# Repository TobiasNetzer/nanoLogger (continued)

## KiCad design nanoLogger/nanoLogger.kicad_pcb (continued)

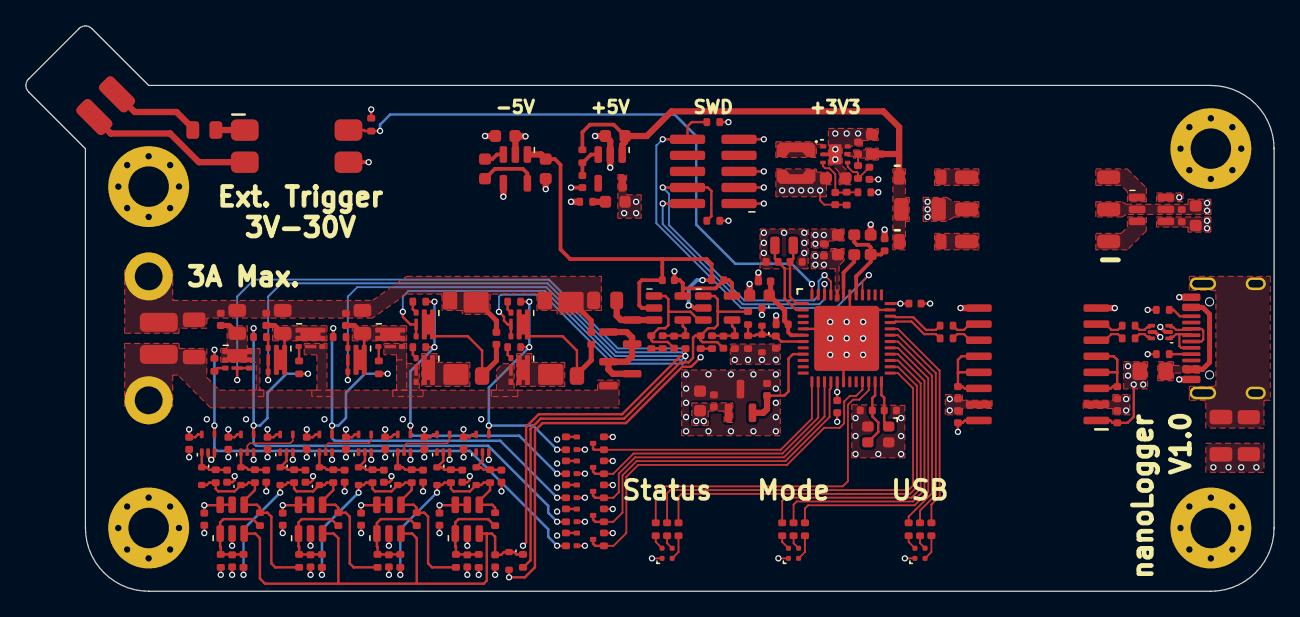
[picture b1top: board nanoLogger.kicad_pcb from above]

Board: 4 copper layers, 98.7 x 44.7 mm, 221 parts (0 on the bottom side), 128 nets.

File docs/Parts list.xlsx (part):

Position | Menge | Bauteilbezeichnung | Wert/Typ | Beschreibung | Hersteller | Hersteller-Nr. | Lieferant | Lieferant-Nr. | Stückpreis | Gesamtpreis
1 | 2 | C1, C35 | 10nF | 10nF-1%-1206-C0G-630V | Kemet | C1206C103FBGACAUTO | Mouser | 80-C1206C103FBGAUTO | 1.03 | 2.06
2 | 6 | C2, C8, C12, C19, C23, C27 | 10µF | 10µF-20%-0603-X5R-10V | Kemet | C0603C106M8PACTU | Mouser | 80-C0603C106M8PACTU | 0.43 | 2.58
3 | 33 | C3, C4, C5, C6, C7, C9, C10, C14, C20, C21, C22, C24, C26, C28, C36, C37, C38, 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 | 100nF | 100nF-20%-0402-X7R-25V | Kemet | C0402C104M3RACTU | Mouser | 80-C0402C104M3R | 0.26 | 8.58
4 | 7 | C11, C43, C44, C50, C51, C52, C53 | 22pF | 22pF-5%-0402-C0G-50V | Kemet | C0402C220J5GACTU | Mouser | 80-C0402C220J5G | 0.09 | 0.63
5 | 2 | C13, C15 | 2.2µF | 2.2µF-10%-0603-X5R-10V | Kemet | C0603C225K8PACTU | Mouser | 80-C0603C225K8P | 0.22 | 0.44
6 | 3 | C16, C17, C18 | 1µF | 1µF-10%-0603-X7R-25V | Kemet | C0603C105K3RACTU | Mouser | 80-C0603C105K3R | 0.26 | 0.78
7 | 1 | C25 | 4.7µF | 4.7µF-20%-0603-X5R-10V | Kemet | C0603C475M8PACTU | Mouser | 80-C0603C475M8P | 0.23 | 0.23
8 | 1 | C29 | 10nF | 10nF-10%-0402-X7R-50V | Kemet | C0402C103K5REC7411 | Mouser | 80-C0402C103K5RECLR | 0.1 | 0.1
9 | 2 | C30, C31 | 8pF | 8pF-0.25pF-0402-C0G-50V | Kemet | CBR04C809C5GAC | Mouser | 80-CBR04C809C5G | 0.12 | 0.24
10 | 2 | C32, C33 | 12pF | 12pF-10%-0402-C0G-25V | Kemet | C0402C120K3GACTU | Mouser | 80-C0402C120K3GACTU | 0.33 | 0.66
11 | 1 | C34 | 100pF | 100pF-5%-0402-C0G-50V | Kemet | C0402C101J5GACTU | Mouser | 80-C0402C101J5G | 0.09 | 0.09
12 | 9 | C45, C54, C55, C56, C57, C58, C59, C60, C61 | 1nF | 1nF-10%-0402-C0G-25V | Kemet | C0402C102K3GACTU | Mouser | 80-C0402C102K3G | 0.27 | 2.4300000000000002
13 | 1 | C70 | 10µF | 10µF-10%-1206-X7R-25V | Kemet | C1206X106K3RACTU | Mouser | 80-C1206X106K3R | 0.94 | 0.94
14 | 2 | D1, D2 | MBR0520L | Schottky Dioden & Gleichrichter 0.5A 20V | onsemi | MBR0520LT3G | Mouser | 863-MBR0520LT3G | 0.36 | 0.72
15 | 3 | D3, D4, D5 | Wuerth_150044M155260 | Standard-LEDs - SMD WL-SFCC SMT LED Full-color Chip | Wuerth Elektronik | 150044M155260 | Mouser | 710-150044M155260 | 0.47 | 1.41
16 | 11 | D6, D7, D8, D9, D10, D11, D12, D13, D14, D15, D16 | 1PS79SB30 | Schottky Diode | Nexperia | 1PS79SB30YL | Mouser | 771-1PS79SB30YL | 0.27 | 2.97
17 | 1 | J1 | USB_Type_C_Receptacle | Receptacle USB - Type C 16 8.94*7.3mm USB Connectors ROHS | Korean Hroparts Elec | USB_C_Receptacle_HRO_TYPE-C-31-M-12 | LCSC | C165948 | 0.28999999999999998 | 0.28999999999999998
18 | 1 | J2 | SWD Header | Sockel & Kabelgehäuse High Reliability Header Strips, 0.050 pitch | Samtec | FTSH-105-01-F-DV-K | Mouser | 200-FTSH10501FDVK | 3.64 | 3.64
19 | 2 | J3, J4 | 2,54mm Steckerleiste | Sockel & Kabelgehäuse .100 Surface Mount Terminal Strip | Samtec | TSM-102-01-F-SH | Mouser | 200-TSM10201FSH | 0.5 | 1
20 | 1 | L1 | 300R 3A | Ferritperlen WE-CBF 0805 200MHz 300Ohm 3000mA AECQ2 | Wuerth Elektronik | 742792031 | Mouser | 710-742792031 | 0.2 | 0.2
21 | 1 | L2 | 2.2µH | 2.2uH Shld 20% 110mOhms AECQ2 | Coilcraft | LPS3015-222MRB | Mouser | 994-LPS3015-222MRB | 1.1299999999999999 | 1.1299999999999999
22 | 1 | L3 | 600R | Ferritperlen 600ohm 25% 440mA | TDK | MMZ1005S601HTD25 | Mouser | 810-MMZ1005S601HTD25 | 0.09 | 0.09
23 | 1 | L4 | 10µH | Festinduktivitäten 0603 10uH 20% | TDK | MLZ1608E100MT | Mouser | 810-MLZ1608E100MT | 0.14000000000000001 | 0.14000000000000001
24 | 9 | Q1, Q2, Q3, Q4, Q5, Q6, Q7, Q8, Q9 | DMN6040SFDE | N-Channel MOSFET | Diodes Incorporated | DMN6040SFDE-7 | Mouser | 621-DMN6040SFDE-7 | 0.59 | 5.31
25 | 2 | Q10, Q11 | MMBTH10L | Bipolartransistor NPN | onsemi | MMBTH10LT3G | Mouser | 863-MMBTH10LT3G | 0.26 | 0.52
26 | 5 | Q12, Q13, Q14, Q15, Q16 | 2N7002T | N-Channel MOSFET | Diodes Incorporated | 2N7002T-7-F | Mouser | 621-2N7002T-F | 0.38 | 1.9
27 | 1 | R1 | 1M | 1M-1%-1206-250mW-50ppm | Yageo | RE1206FRE071ML | Mouser | 603-RE1206FRE071ML | 0.12 | 0.12
28 | 2 | R2, R3 | 5k1 | 5.1k-1%-0402-62.5mW-50ppm | Yageo | RT0402FRE075K1L | Mouser | 603-RT0402FRE075K1L | 0.09 | 0.18
29 | 4 | R4, R5, R6, R7 | 24R | 24R-1%-0402-62.5mW-50ppm | Yageo | RT0402FRE0724RL | Mouser | 603-RT0402FRE0724RL | 0.22 | 0.88
30 | 10 | R8, R11, R14, R48, R50, R52, R54, R56, R60, R66 | 10k | 10k-1%-0402-62.5mW-50ppm | Yageo | RT0402FRE0710KL | Mouser | 603-RT0402FRE0710KL | 0.22 | 2.2000000000000002
31 | 1 | R9 | 820k | 820k-1%-0402-62.5mW-100ppm | Yageo | RC0402FR-07820KL | Mouser | 603-RC0402FR-07820KL | 0.09 | 0.09
32 | 1 | R10 | 182k | 182k-1%-0402-62.5mW-50ppm | Yageo | RT0402FRE07182KL | Mouser | 603-RT0402FRE07182KL | 0.09 | 0.09
33 | 1 | R12 | 1R | 1R-1%-0402-62.5mW-50ppm | Bourns | CRT0402-FZ-1R00GLF | Mouser | 652-CRT0402FZ1R00GLF | 0.09 | 0.09
34 | 5 | R13, R15, R18, R21, R59 | 1k | 1k-1%-0402-62.5mW-50ppm | Yageo | RT0402FRE071KL | Mouser | 603-RT0402FRE071KL | 0.09 | 0.44999999999999996
35 | 3 | R16, R19, R22 | 2k8 | 2k8-1%-0402-62.5mW-50ppm | Yageo | RT0402FRE072K8L | Mouser | 603-RT0402FRE072K8L | 0.22 | 0.66
36 | 3 | R17, R20, R23 | 1k5 | 1k5-1%-0402-62.5mW-50ppm | Yageo | RT0402FRE131K5L | Mouser | 603-RT0402FRE131K5L | 0.22 | 0.66
37 | 2 | R24, R25 | 10k 0.05% | 10k-0.05%-0402-62.5mW-10ppm | Susumu | RG1005N-103-W-T1 | Mouser | 754-RG1005N-103-WT1 | 1.05 | 2.1
38 | 1 | R26 | 10k 0,05% | 10k-0.05%-0805-1/8W-10ppm | Susumu | RG2012N-103-W-T1 | Mouser | 754-RG2012N-103-W-T1 | 0.83 | 0.83
39 | 1 | R27 | 100R 0,05% | 100R-0.05%-0805-1/8W-10ppm | Susumu | RG2012N-101-W-T1 | Mouser | 754-RG2012N-101-W-T1 | 0.81 | 0.81
40 | 1 | R28 | 10R 0,05% | 10R-0.05%-0805-1/8W-10ppm | Stackpole | RNCF0805AKT10R0 | Digikey | RNCF0805AKT10R0CT-ND | 0.89 | 0.89
41 | 1 | R29 | 100m 0,1% | 100m-0.1%-2512-1W-15ppm | Vishay Precision Group | Y14870R10000B9R | Mouser | 71-CSM25120R1000BST | 8.09 | 8.09
42 | 1 | R30 | 10m 0,1% | 10m-0.1%-2512-1W-15ppm | Vishay Precision Group | Y14870R01000B9R | Mouser | 71-CSM25120R0100BST | 7.39 | 7.39
43 | 1 | R31 | 220R | 220R-1%-0805-250mW-100ppm | Yageo | RC0805JR-13220RL | Mouser | 603-RC0805JR-13220RL | 0.09 | 0.09
44 | 2 | R32, R35 | 2k2 0,05% | 2.2k-0.05%-0402-100mW-10ppm | Panasonic Electronic Components | ERA-2VRW2201X | Digikey | 10-ERA-2VRW2201XCT-ND | 0.75 | 1.5
45 | 2 | R33, R36 | 6k8 0,05% | 6.8k-0.05%-0402-100mW-10ppm | Panasonic Electronic Components | ERA-2VRW6801X | Digikey | 10-ERA-2VRW6801XCT-ND | 0.75 | 1.5
46 | 2 | R34, R37 | 1k 0,05% | 1k-0.05%-0402-62.5mW-5ppm | Susumu | RG1005V-102-W-T1 | Mouser | 754-RG1005V-102-WT1 | 3.12 | 6.24
47 | 14 | R38, R39, R40, R41, R42, R43, R44, R45, R46, R47, R49, R51, R53, R55 | 68R | 68R-1%-0402-62.5mW-100ppm | Yageo | RC0402FR-0768RL | Mouser | 603-RC0402FR-0768RL | 0.09 | 1.26
48 | 1 | R57 | 10k | 10k-1%-0805-330mW-200ppm | Yageo | SR0805FR-7T10KL | Mouser | 603-SR0805FR-7T10KL | 0.7 | 0.7
49 | 1 | R58 | 100k | 100k-1%-0402-62.5mW-50ppm | Yageo | RT0402FRE07100KL | Mouser | 603-RT0402FRE07100KL | 0.09 | 0.09
50 | 2 | R61, R67 | 15k | 15k-1%-0402-62.5mW-100ppm | Vishay/Dale | CRCW040215K0FKEDC | Mouser | 71-CRCW040215K0FKEDC | 0.09 | 0.18
51 | 2 | R62, R68 | 7M5 | 7.5M-1%-0402-62.5mW-100ppm | Vishay/Dale | CRCW04027M50FKED | Mouser | 71-CRCW04027M50FKED | 0.09 | 0.18
52 | 2 | R63, R69 | 24k | 24k-1%-0402-62.5mW-100ppm | Bourns | CR0402-FX-2402GLF | Mouser | 652-CR0402FX-2402GLF | 0.09 | 0.18
53 | 2 | R64, R70 | 36k | 36k-1%-0402-62.5mW-100ppm | Bourns | CR0402-FX-3602GLF | Mouser | 652-CR0402FX-3602GLF | 0.09 | 0.18
54 | 2 | R65, R71 | 750k | 750k-1%-0402-62.5mW-100ppm | Bourns | CR0402-FX-7503GLF | Mouser | 652-CR0402FX-7503GLF | 0.09 | 0.18
55 | 8 | R72, R73, R74, R75, R76, R77, R78, R79 | 100R | 100R-1%-0402-62.5mW-50ppm | Yageo | RT0402FRE07100RL | Mouser | 603-RT0402FRE07100RL | 0.09 | 0.72
56 | 1 | TR1 | Wuerth_750315371 | Netztransformatoren MID-SN6505 TI Driver 5V 1A 320 to 480kHz | Wuerth Elektronik | 750315371 | Mouser | 710-750315371 | 2.36 | 2.36
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
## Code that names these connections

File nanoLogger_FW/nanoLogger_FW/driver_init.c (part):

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{
	init_mcu();

	// GPIO on PA08

	// Set pin direction to input
	gpio_set_pin_direction(RANGE_SWITCH_POSITION_5, GPIO_DIRECTION_IN);
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
	gpio_set_pin_function(RANGE_SWITCH_POSITION_5, GPIO_PIN_FUNCTION_OFF);

	// GPIO on PA09

	// Set pin direction to input
	gpio_set_pin_direction(RANGE_SWITCH_POSITION_4, GPIO_DIRECTION_IN);
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
	gpio_set_pin_function(RANGE_SWITCH_POSITION_4, GPIO_PIN_FUNCTION_OFF);

	// GPIO on PA10

	// Set pin direction to input
	gpio_set_pin_direction(RANGE_SWITCH_POSITION_3, GPIO_DIRECTION_IN);
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
	gpio_set_pin_function(RANGE_SWITCH_POSITION_3, GPIO_PIN_FUNCTION_OFF);

	// GPIO on PA11

	// Set pin direction to input
	gpio_set_pin_direction(RANGE_SWITCH_POSITION_2, GPIO_DIRECTION_IN);
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
	gpio_set_pin_function(RANGE_SWITCH_POSITION_2, GPIO_PIN_FUNCTION_OFF);

	// GPIO on PA12

	// Set pin direction to input
	gpio_set_pin_direction(RANGE_SWITCH_POSITION_1, GPIO_DIRECTION_IN);
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
	gpio_set_pin_function(RANGE_SWITCH_POSITION_1, GPIO_PIN_FUNCTION_OFF);

	// GPIO on PA13

	gpio_set_pin_level(STATUS_LED_RED,
	                   // <y> Initial level
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
	gpio_set_pin_function(STATUS_LED_RED, GPIO_PIN_FUNCTION_OFF);

	// GPIO on PA16

	gpio_set_pin_level(STATUS_LED_GREEN,
	                   // <y> Initial level
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
	gpio_set_pin_function(STATUS_LED_GREEN, GPIO_PIN_FUNCTION_OFF);

	// GPIO on PA17

	gpio_set_pin_level(STATUS_LED_BLUE,
	                   // <y> Initial level
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
	gpio_set_pin_function(STATUS_LED_BLUE, GPIO_PIN_FUNCTION_OFF);

	// GPIO on PA18

	gpio_set_pin_level(MODE_LED_RED,
	                   // <y> Initial level
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
	gpio_set_pin_function(MODE_LED_RED, GPIO_PIN_FUNCTION_OFF);

	// GPIO on PA19

	gpio_set_pin_level(MODE_LED_GREEN,
	                   // <y> Initial level
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
	gpio_set_pin_function(MODE_LED_GREEN, GPIO_PIN_FUNCTION_OFF);

	// GPIO on PA20

	gpio_set_pin_level(MODE_LED_BLUE,
	                   // <y> Initial level
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
	gpio_set_pin_function(MODE_LED_BLUE, GPIO_PIN_FUNCTION_OFF);

	// GPIO on PA21

	gpio_set_pin_level(USB_STATUS_LED_RED,
	                   // <y> Initial level
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
	gpio_set_pin_function(USB_STATUS_LED_RED, GPIO_PIN_FUNCTION_OFF);

	// GPIO on PA22

	gpio_set_pin_level(USB_STATUS_LED_GREEN,
	                   // <y> Initial level
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
	gpio_set_pin_function(USB_STATUS_LED_GREEN, GPIO_PIN_FUNCTION_OFF);

	// GPIO on PA23

	gpio_set_pin_level(USB_STATUS_LED_BLUE,
	                   // <y> Initial level
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
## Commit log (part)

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2025-08-25 add docs
2025-08-28 fix typo
2025-08-28 rename images
